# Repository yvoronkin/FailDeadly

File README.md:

# FailDeadly
### Fail Secure. Fail Deadly

FailDeadly is a USB hardware device designed to ensure the physical security of the server. It uses Hall sensors, along with magnets installed on the server lid, to detect any tampering attempt. To make it work, FailDeadly integrates with infrastructure and becomes the main or one of the sources of trust to pass server remote attestation.

FailDeadly stores secrets such as the sign key in SRAM as long as the MCU has power. In case of a tampering attempt when the server lid is moved, device power management detects a change in the magnetic field and cuts off the MCU power supply. FailDeadly destroy in memory secret in one second or less after the tamper event is detected. This time delay allows the MCU to notify the host system about the tamper event through message, SysRq, or hardware reset event.

To be able to keep secrets and reduce the number of maintenance events during power outages, FailDeadly has an Ionister to keep the SRAM powered.

### ** _Warning:_ FailDeadly achives it goals by valuing confidentiality more than availability. Be aware.**

Features:

* Physical tamper detection
* In-memory secret storage
* Power cut off on bare logic - no way to cancel 
* Secret destruction in case of tampering event
* SysRq or Reset pin could be used to reset the host system.
* On-board ionistor connector to keep secrets through power outages
* HashiCorp Vault integration
* On-device encrypt/decrypt, sign/verity operations.
* On-device key generation

Use cases:

* Hardening server physical security
* Remote server attestation
* Burn-out LUKS decryption keys

### TODO:
- [x] Hardware design v1.0 rev 001 
- [ ] Firmware 
- [ ] Software 
- [ ] HashiCorp Vault login plugin

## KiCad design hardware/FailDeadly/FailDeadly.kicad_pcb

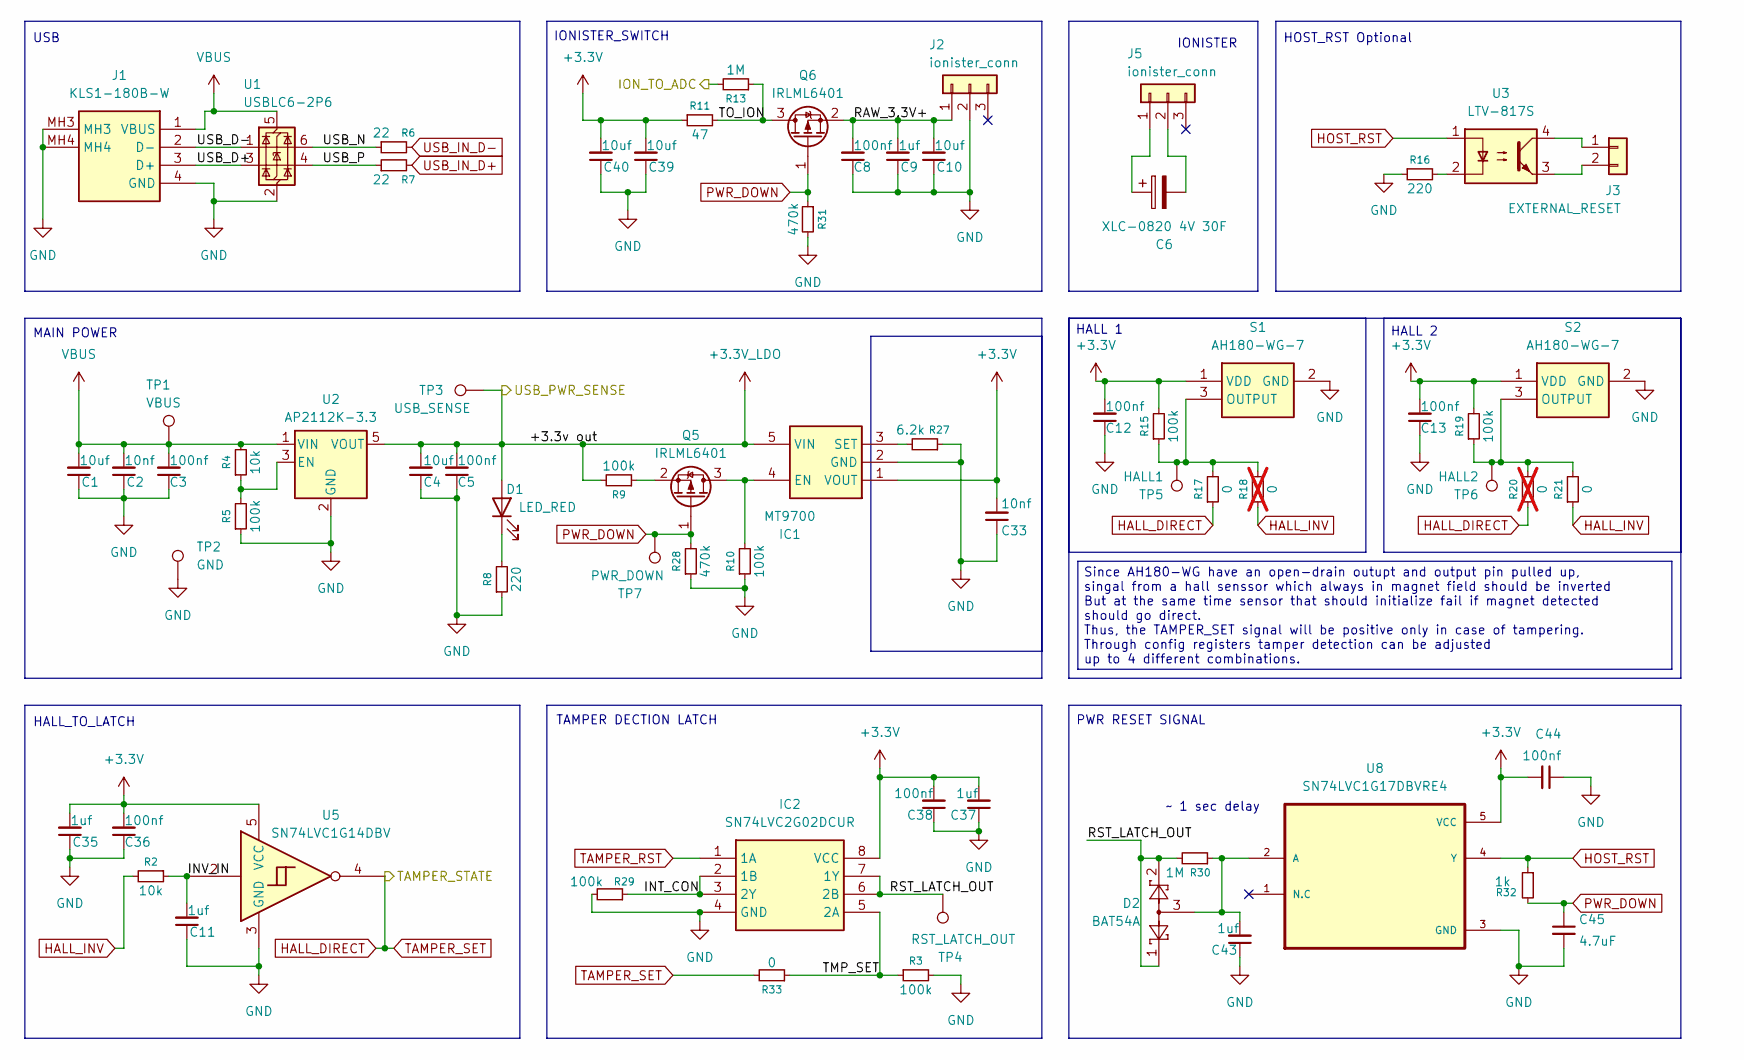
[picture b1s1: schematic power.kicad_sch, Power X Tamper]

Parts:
C1, C4, C10, C39, C40: 10uf; C_0603_1608Metric
C2, C33: 10nf; C_0402_1005Metric
C3, C5, C8, C12, C13, C36, C38, C44: 100nf; C_0402_1005Metric
C6: XLC-0820 4V 30F
C9, C11, C35, C37, C43: 1uf; C_0402_1005Metric
C45: 4.7uF; C_0603_1608Metric
D1: LED_RED; LED_0805_2012Metric
D2: BAT54A; SOT-23
IC1: MT9700; SOT95P280X135-5N; Manufacturer_Part_Number MT9700
IC2: SN74LVC2G02DCUR; SOP50P310X90-8N; Manufacturer_Part_Number SN74LVC2G02DCUR; Mouser Part Number 595-SN74LVC2G02DCUR
J1: KLS1-180B-W; KLS1180BW; Manufacturer_Part_Number KLS1-180B-W
J2, J5: ionister_conn; JST_XH_B3B-XH-AM_1x03_P2.50mm_Vertical
J3: EXTERNAL_RESET; PinHeader_1x02_P2.54mm_Vertical
Q5, Q6: IRLML6401; SOT-23
R2, R4: 10k; R_0402_1005Metric
R3, R5, R9, R10, R15, R19, R29: 100k; R_0402_1005Metric
R6, R7: 22; R_0402_1005Metric
R8, R16: 220; R_0402_1005Metric
R11: 47; R_0603_1608Metric
R13, R30: 1M; R_0402_1005Metric
R17, R21, R33: 0; R_0402_1005Metric
R18, R20: 0; R_0402_1005Metric; not fitted
R27: 6.2k; R_0402_1005Metric
R28, R31: 470k; R_0402_1005Metric
R32: 1k; R_0402_1005Metric
S1, S2: AH180-WG-7; AH180WG7; Manufacturer_Part_Number AH180-WG-7; Mouser Part Number 621-AH180-WG-7
TP1: VBUS; TestPoint_Pad_D1.5mm
TP2: GND; TestPoint_Pad_D2.5mm
TP3: USB_SENSE; TestPoint_Pad_D1.5mm
TP4: RST_LATCH_OUT; TestPoint_Pad_D1.5mm
TP5: HALL1; TestPoint_Pad_D1.5mm
TP6: HALL2; TestPoint_Pad_D1.5mm
TP7: PWR_DOWN; TestPoint_Pad_D1.5mm
U1: USBLC6-2P6; SOT-666
U2: AP2112K-3.3; SOT-23-5
U3: LTV-817S; SMDIP-4_W9.53mm
U5: SN74LVC1G14DBV; SOT-23-5
U8: SN74LVC1G17DBVRE4; SOT95P280X145-5N

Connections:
+3.3V: C12.2, C13.2, C33.2, C35.2, C36.2, C37.2, C38.2, C39.2, C40.2, C44.2, IC1.1 (VOUT), IC2.8 (VCC), R11.1, R15.2, R19.2, S1.1 (VDD), S2.1 (VDD), U5.5 (VCC), U8.5 (VCC); also elsewhere on the board
+3.3V_LDO: C4.2, C5.2, D1.2 (A), IC1.5 (VIN), R9.2, TP3.1 (1_1), U2.5 (VOUT); also elsewhere on the board
/MCU/ION_TO_ADC: R13.2; also elsewhere on the board
/Power/INT_CON: IC2.2 (1B), IC2.3 (2Y), R29.1
/Power/INV_IN: C11.2, R2.1, U5.2
/Power/RAW_3.3V+: C8.2, C9.2, C10.2, J2.1, Q6.2 (S)
/Power/RST_LATCH_OUT: D2.1, D2.2, IC2.6 (2B), IC2.7 (1Y), R30.2, TP4.1 (1_1)
/Power/TMP_SET: IC2.5 (2A), R3.1, R33.1
/Power/TO_ION: Q6.3 (D), R11.2, R13.1
/Power/USB_D+: J1.3 (D+), U1.3 (I/O2)
/Power/USB_D-: J1.2 (D-), U1.1 (I/O1)
/Power/USB_N: R6.1, U1.6 (I/O1)
/Power/USB_P: R7.1, U1.4 (I/O2)
GND: C1.1, C2.1, C3.1, C4.1, C5.1, C8.1, C9.1, C10.1, C11.1, C12.1, C13.1, C33.1, C35.1, C36.1, C37.1, C38.1, C39.1, C40.1, C43.1, C44.1, C45.2, IC1.2 (GND), IC2.4 (GND), J1.4 (GND), J1.MH3, J1.MH4, J2.2, R3.2, R5.1, R8.1, R10.1, R16.1, R27.1, R28.1, R29.2, R31.2, S1.2 (GND), S2.2 (GND), TP2.1 (1_1), U1.2 (GND), U2.2 (GND), U5.3 (GND), U8.3 (GND); also elsewhere on the board
HALL_DIRECT: R17.1, R20.1, R33.2, U5.4; also elsewhere on the board
HALL_INV: R2.2, R18.1, R21.1
HOST_RST: R32.1, U3.1, U8.4 (Y)
unnamed: C6.1, J5.1
unnamed: C6.2, J5.2
unnamed: D1.1 (K), R8.2
unnamed: IC1.4 (EN), Q5.3 (D), R10.2
unnamed: IC1.3 (SET), R27.2
unnamed: J3.1, U3.4
unnamed: J3.2, U3.3
unnamed: Q5.2 (S), R9.1
unnamed: R16.2, U3.2
unnamed: R15.1, R17.2, R18.2, S1.3 (OUTPUT), TP5.1 (1_1)
unnamed: R19.1, R20.2, R21.2, S2.3 (OUTPUT), TP6.1 (1_1)
unnamed: R4.1, R5.2, U2.3 (EN)
unnamed: C43.2, D2.3, R30.1, U8.2 (A)
PWR_DOWN: C45.1, Q5.1 (G), Q6.1 (G), R28.2, R31.1, R32.2, TP7.1 (1_1); also elsewhere on the board
TAMPER_RST: IC2.1 (1A); also elsewhere on the board
USB_IN_D+: R7.2; also elsewhere on the board
USB_IN_D-: R6.2; also elsewhere on the board
VBUS: C1.2, C2.2, C3.2, J1.1 (VBUS), R4.2, TP1.1 (1_1), U1.5 (VBUS), U2.1 (VIN)

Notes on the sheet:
HALL_TO_LATCH
USB
~ 1 sec delay
IONISTER
HALL 2
TAMPER DECTION LATCH
MAIN POWER
HOST_RST Optional
HALL 1
PWR RESET SIGNAL
Since AH180-WG have an open-drain outupt and output pin pulled up, singal from a hall senssor which always in magnet field should be inverted But at the same time sensor that should initialize fail if magnet detected should go direct. Thus, the TAMPER_SET signal will be positive only in case of tam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
IONISTER_SWITCH

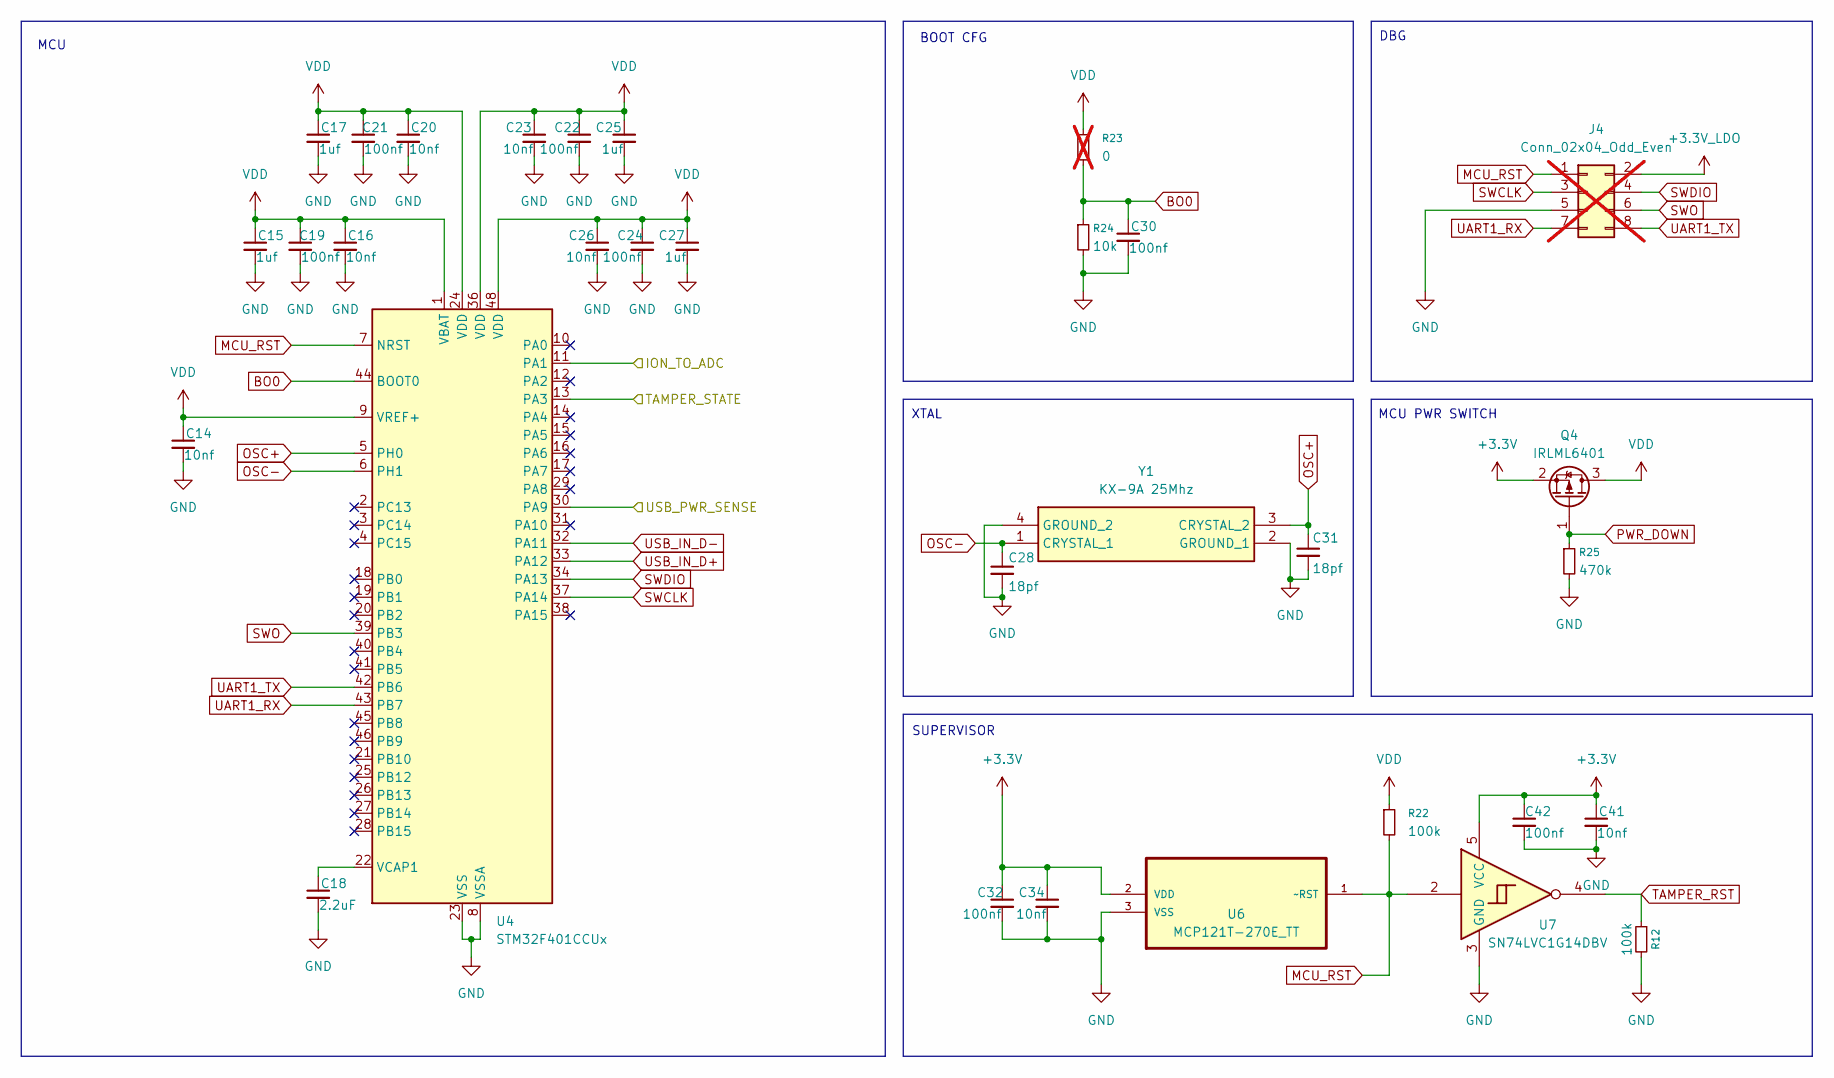
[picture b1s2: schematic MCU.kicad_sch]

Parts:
C14, C16, C20, C23, C26, C34, C41: 10nf; C_0402_1005Metric
C15, C17, C25, C27: 1uf; C_0402_1005Metric
C18: 2.2uF; C_0603_1608Metric
C19, C21, C22, C24, C30, C32, C42: 100nf; C_0402_1005Metric
C28, C31: 18pf; C_0402_1005Metric
J4: Conn_02x04_Odd_Even; PinHeader_2x04_P2.54mm_Vertical_SMD; not fitted
Q4: IRLML6401; SOT-23
R12, R22: 100k; R_0402_1005Metric
R23: 0; R_0402_1005Metric; not fitted
R24: 10k; R_0402_1005Metric
R25: 470k; R_0402_1005Metric
U4: STM32F401CCUx; QFN-48-1EP_7x7mm_P0.5mm_EP5.6x5.6mm
U6: MCP121T-270E_TT; SOT95P237X112-3N; MPN MCP121T-270E/TT
U7: SN74LVC1G14DBV; SOT-23-5
Y1: KX-9A 25Mhz; KX9A; Manufacturer_Part_Number KX-9A

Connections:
+3.3V: C32.1, C34.1, C41.1, C42.1, Q4.2 (S), U6.2 (VDD), U7.5 (VCC); also elsewhere on the board
+3.3V_LDO: J4.2, U4.30 (PA9); also elsewhere on the board
/MCU/ION_TO_ADC: U4.11 (PA1); also elsewhere on the board
BO0: C30.1, R23.2, R24.1, U4.44 (BOOT0)
GND: C14.2, C15.2, C16.2, C17.2, C18.2, C19.2, C20.2, C21.2, C22.2, C23.2, C24.2, C25.2, C26.2, C27.2, C28.2, C30.2, C31.2, C32.2, C34.2, C41.2, C42.2, J4.5, R12.2, R24.2, R25.2, U4.8 (VSSA), U4.23 (VSS), U4.35 (VSS), U4.47 (VSS), U4.49 (VSS), U6.3 (VSS), U7.3 (GND), Y1.2 (GROUND_1), Y1.4 (GROUND_2); also elsewhere on the board
HALL_DIRECT: U4.13 (PA3); also elsewhere on the board
MCU_RST: J4.1, R22.2, U4.7 (NRST), U6.1 (~RST), U7.2
unnamed: C18.1, U4.22 (VCAP1)
OSC+: C31.1, U4.5 (PH0), Y1.3 (CRYSTAL_2)
OSC-: C28.1, U4.6 (PH1), Y1.1 (CRYSTAL_1)
PWR_DOWN: Q4.1 (G), R25.1; also elsewhere on the board
SWCLK: J4.3, U4.37 (PA14)
SWDIO: J4.4, U4.34 (PA13)
SWO: J4.6, U4.39 (PB3)
TAMPER_RST: R12.1, U7.4; also elsewhere on the board
UART1_RX: J4.7, U4.43 (PB7)
UART1_TX: J4.8, U4.42 (PB6)
USB_IN_D+: U4.33 (PA12); also elsewhere on the board
USB_IN_D-: U4.32 (PA11); also elsewhere on the board
VDD: C14.1, C15.1, C16.1, C17.1, C19.1, C20.1, C21.1, C22.1, C23.1, C24.1, C25.1, C26.1, C27.1, Q4.3 (D), R22.1, R23.1, U4.1 (VBAT), U4.9 (VREF+), U4.24 (VDD), U4.36 (VDD), U4.48 (VDD)

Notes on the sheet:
SUPERVISOR
MCU PWR SWITCH
DBG
BOOT CFG
XTAL
MCU

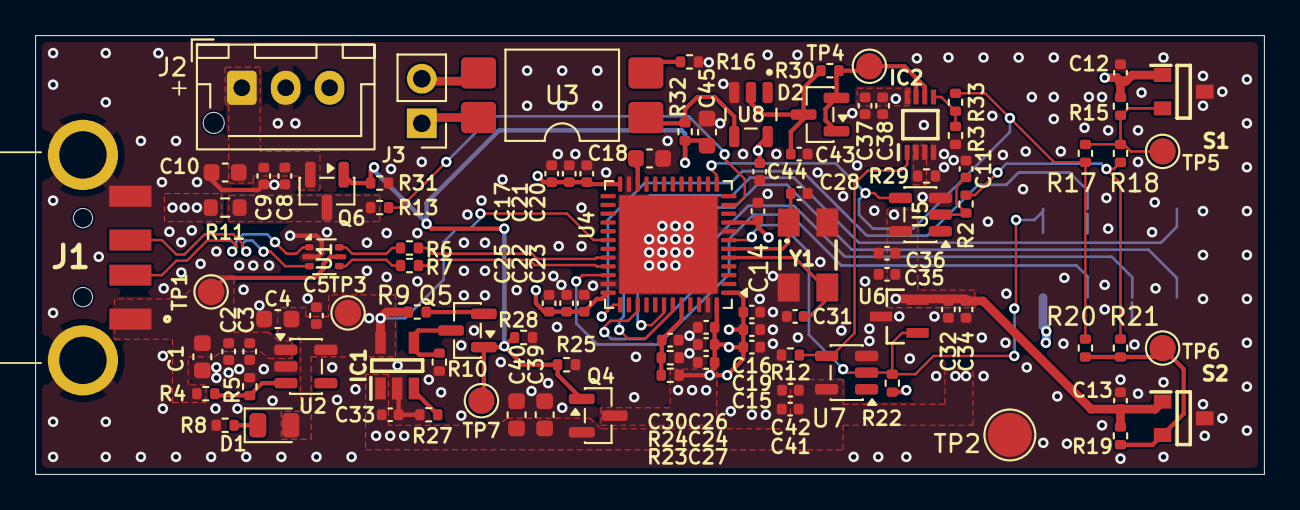
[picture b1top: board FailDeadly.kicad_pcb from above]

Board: 4 copper layers, 70.0 x 25.0 mm, 101 parts (1 on the bottom side), 44 nets.

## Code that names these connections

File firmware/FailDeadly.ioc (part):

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Mcu.Name=STM32F401C(B-C)Ux
Mcu.Package=UFQFPN48
Mcu.UserName=STM32F401CCUx
PA1.GPIOParameters=GPIO_Label
PA1.GPIO_Label=ion_to_adc
PA1.Signal=ADCx_IN1
PA11.Mode=Device_Only
PA11.Signal=USB_OTG_FS_DM
PA12.Mode=Device_Only
PA12.Signal=USB_OTG_FS_DP
PA13.Mode=Serial_Wire
PA13.Signal=SYS_JTMS-SWDIO
PA14.Mode=Serial_Wire
PA14.Signal=SYS_JTCK-SWCLK
PA3.GPIOParameters=GPIO_Label
PA3.GPIO_Label=tamper_state
PA3.Signal=GPXTI3
PA9.GPIOParameters=GPIO_Label,GPIO_ModeDefaultEXTI
PA9.GPIO_Label=usb_power_sense
PA9.GPIO_ModeDefaultEXTI=GPIO_MODE_IT_RISING_FALLING
PA9.Signal=GPXTI9
PB6.Mode=Asynchronous
PB6.Signal=USART1_TX
PB7.Mode=Asynchronous
PB7.Signal=USART1_RX
PC13-ANTI_TAMP.GPIOParameters=GPIO_Label
PC13-ANTI_TAMP.GPIO_Label=debug_led
PC13-ANTI_TAMP.Signal=GPIO_Output
PH0\ -\ OSC_IN.Mode=HSE-External-Oscillator
PH0\ -\ OSC_IN.Signal=RCC_OSC_IN
PH1\ -\ OSC_OUT.Mode=HSE-External-Oscillator
PH1\ -\ OSC_OUT.Signal=RCC_OSC_OUT
RCC.HSE_VALUE=25000000
RCC.SYSCLKFreq_VALUE=60000000
RCC.SYSCLKSource=RCC_SYSCLKSOURCE_PLLCLK
board=custom
